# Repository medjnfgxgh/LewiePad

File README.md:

# LewiePad
A 12 key macropad powered by a rp2040. Featuring a rotary encoder and 2 neopixels.

Schematic:

PCB:

Cad:

Finished macropad:

BOM:
 - 12x MX-Style switches
 - 1x EC11 Rotary encoder
 - 2x SK6812 MINI Leds
 - 1x XIAO RP2040
 - 12x Blank DSA Keycaps
 - 4x M3x16 Bolt
 - 4x M3 Heatset

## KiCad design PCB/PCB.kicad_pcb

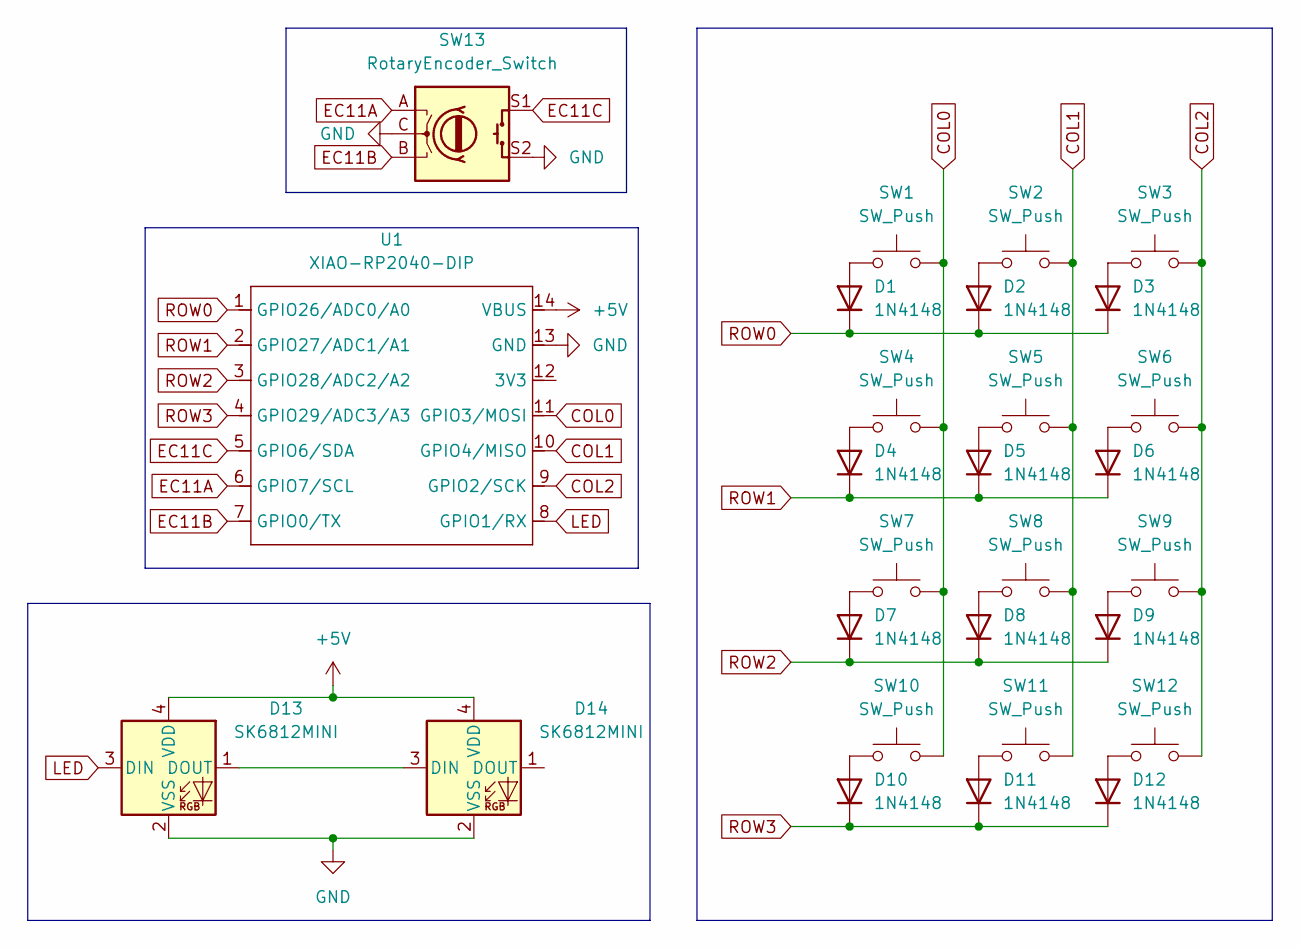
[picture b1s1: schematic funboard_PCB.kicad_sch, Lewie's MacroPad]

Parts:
D1, D2, D3, D4, D5, D6, D7, D8, D9, D10, D11, D12: 1N4148; D_DO-35_SOD27_P7.62mm_Horizontal
D13, D14: SK6812MINI; LED_SK6812MINI_PLCC4_3.5x3.5mm_P1.75mm
SW1, SW2, SW3, SW4, SW5, SW6, SW7, SW8, SW9, SW10, SW11, SW12: SW_Push; SW_Cherry_MX_1.00u_PCB
SW13: RotaryEncoder_Switch; RotaryEncoder_Alps_EC11E-Switch_Vertical_H20mm
U1: XIAO-RP2040-DIP

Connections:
+5V: D13.4 (VDD), D14.4 (VDD), U1.14 (VBUS)
COL0: SW1.2, SW4.2, SW7.2, SW10.2, U1.11 (GPIO3/MOSI)
COL1: SW2.2, SW5.2, SW8.2, SW11.2, U1.10 (GPIO4/MISO)
COL2: SW3.2, SW6.2, SW9.2, SW12.2, U1.9 (GPIO2/SCK)
EC11A: SW13.A, U1.6 (GPIO7/SCL)
EC11B: SW13.B, U1.7 (GPIO0/TX)
EC11C: SW13.S1, U1.5 (GPIO6/SDA)
GND: D13.2 (VSS), D14.2 (VSS), SW13.C, SW13.S2, U1.13 (GND)
LED: D13.3 (DIN), U1.8 (GPIO1/RX)
unnamed: D1.2 (A), SW1.1
unnamed: D2.2 (A), SW2.1
unnamed: D3.2 (A), SW3.1
unnamed: D4.2 (A), SW4.1
unnamed: D5.2 (A), SW5.1
unnamed: D6.2 (A), SW6.1
unnamed: D7.2 (A), SW7.1
unnamed: D8.2 (A), SW8.1
unnamed: D9.2 (A), SW9.1
unnamed: D10.2 (A), SW10.1
unnamed: D11.2 (A), SW11.1
unnamed: D12.2 (A), SW12.1
unnamed: D13.1 (DOUT), D14.3 (DIN)
ROW0: D1.1 (K), D2.1 (K), D3.1 (K), U1.1 (GPIO26/ADC0/A0)
ROW1: D4.1 (K), D5.1 (K), D6.1 (K), U1.2 (GPIO27/ADC1/A1)
ROW2: D7.1 (K), D8.1 (K), D9.1 (K), U1.3 (GPIO28/ADC2/A2)
ROW3: D10.1 (K), D11.1 (K), D12.1 (K), U1.4 (GPIO29/ADC3/A3)

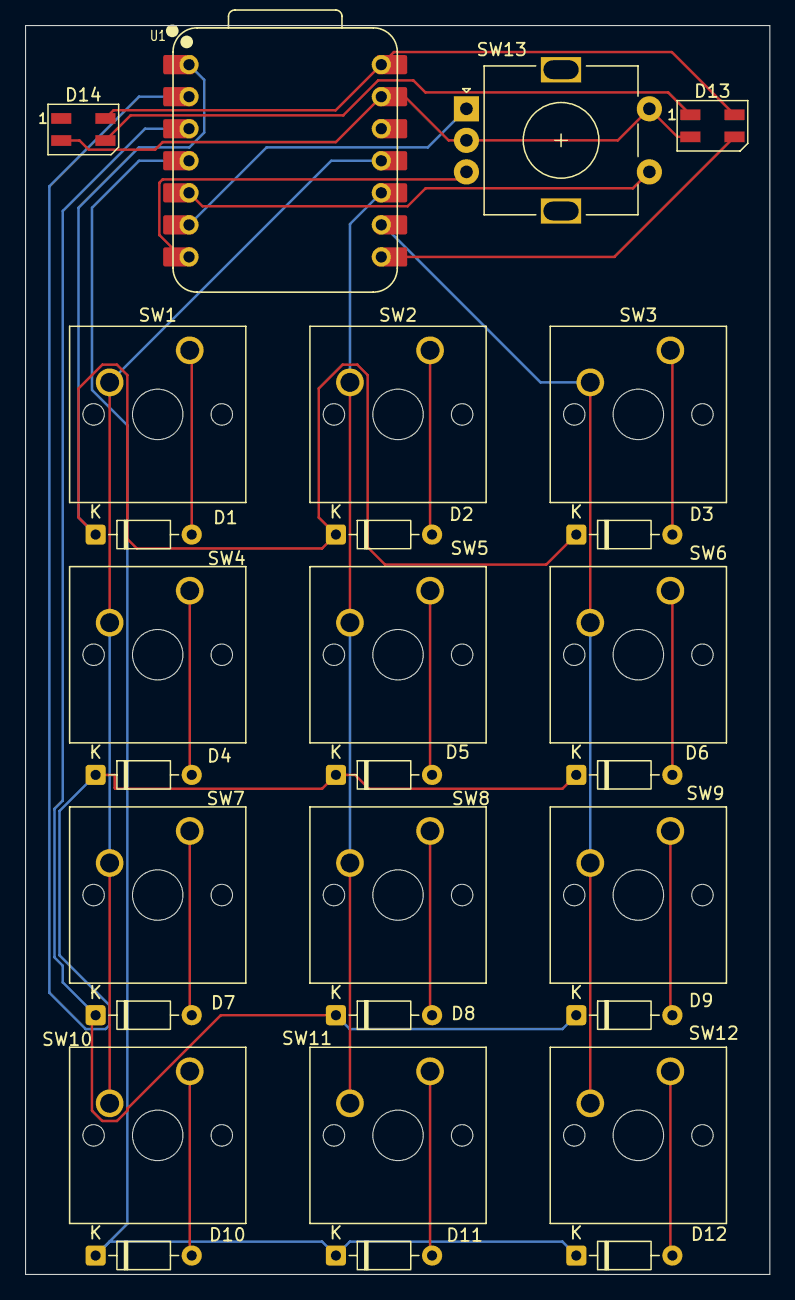
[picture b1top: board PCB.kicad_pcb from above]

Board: 2 copper layers, 59.0 x 99.0 mm, 28 parts (0 on the bottom side), 26 nets.

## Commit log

2025-12-19 added PCB and firmware
2025-12-19 pcb and cad
2026-01-31 fixed keys and decoder
2026-02-12 firmware fixes
2026-02-21 added image
